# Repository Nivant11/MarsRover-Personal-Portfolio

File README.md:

# This is my personal portfolio of work that I have done on Cornell Mars Rover

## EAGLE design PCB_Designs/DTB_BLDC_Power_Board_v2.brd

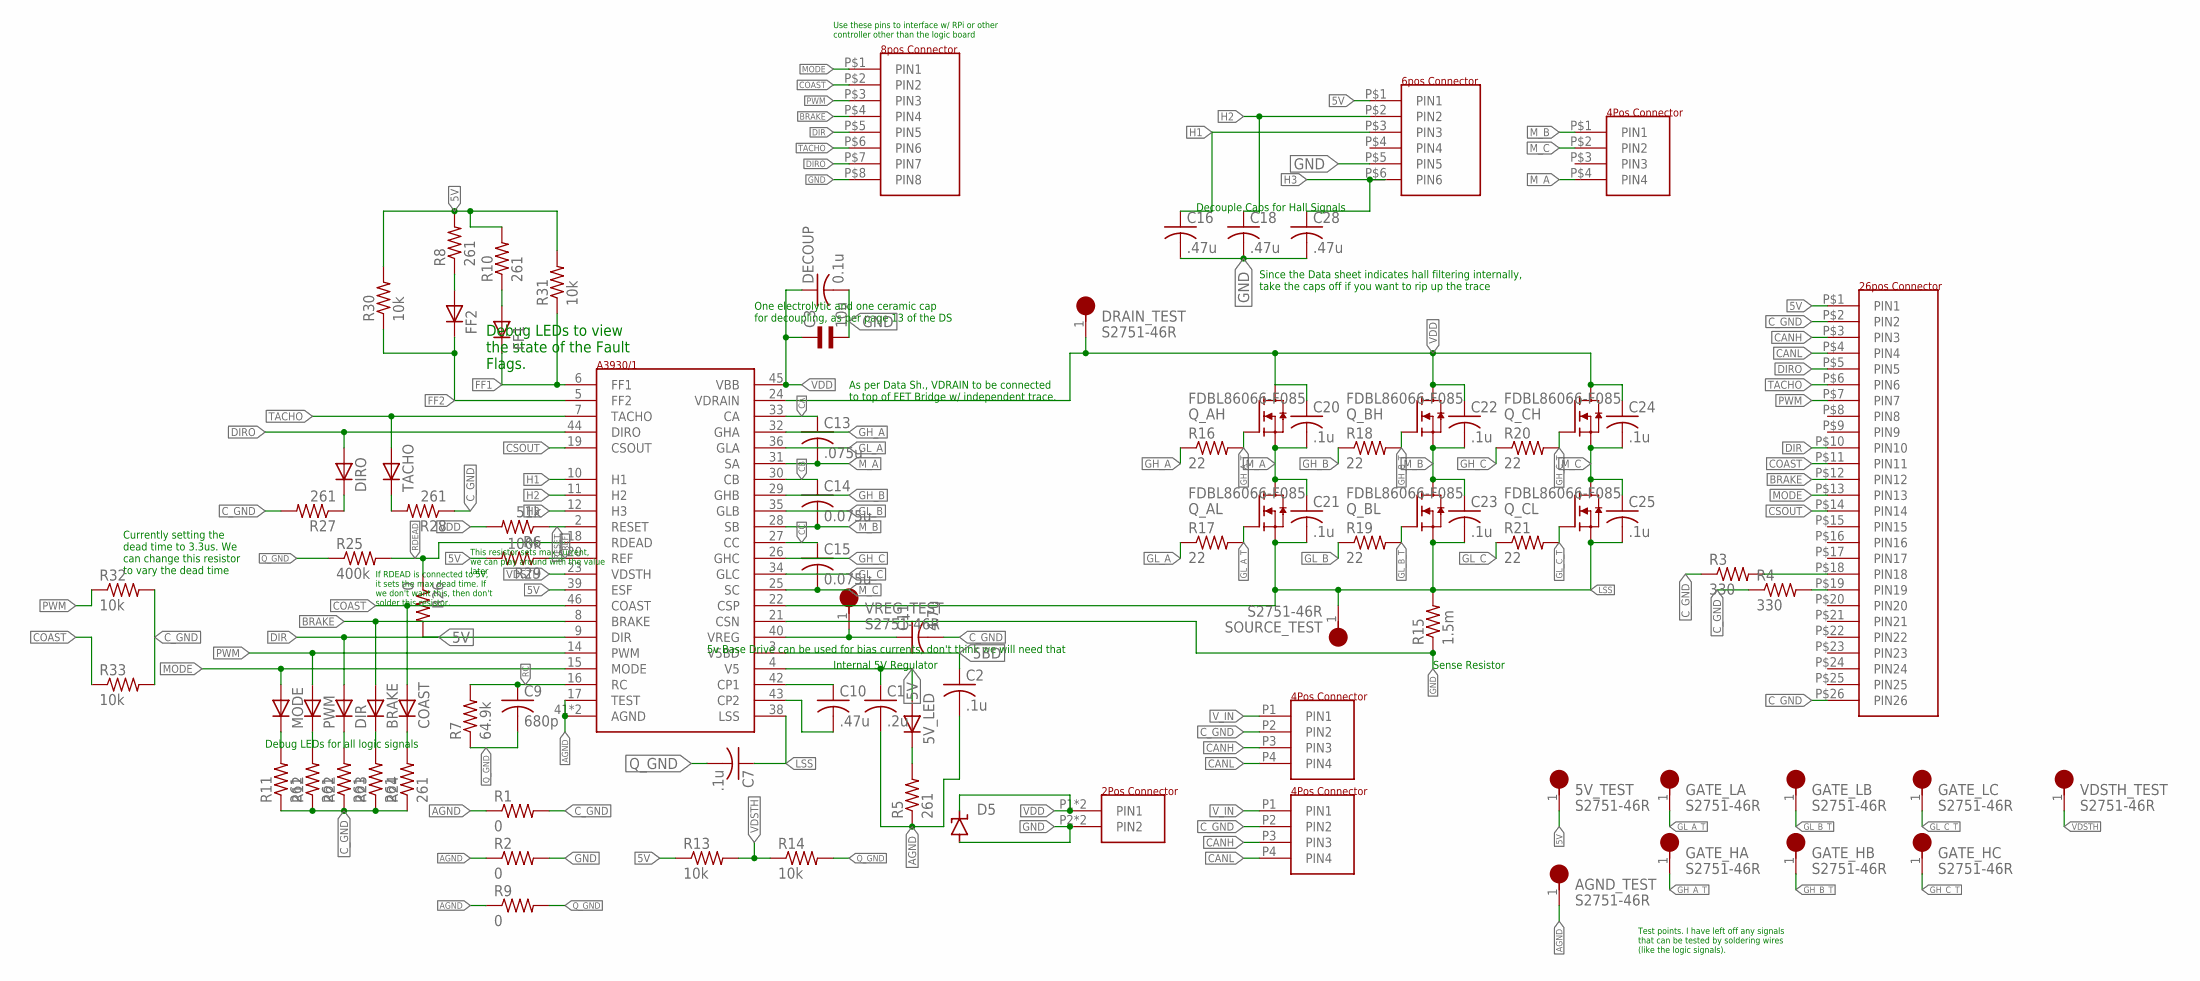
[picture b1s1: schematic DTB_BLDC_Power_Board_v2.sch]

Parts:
5V_LED: LED0603; DO0603
5V_TEST: S2751-46R; HARWIN_S2751-46R
AGND_TEST: S2751-46R; HARWIN_S2751-46R
BRAKE: LED0603; DO0603
C1: .2u; C1206K
C2, C20, C21, C22, C23, C24, C25: .1u; C1206K
C3: 10u; EU25-10
C7: .1u; C0603
C9: 680p; C0603K
C10: .47u; C1206K
C11: 4.7u; C1206K
C13: .075u; C1206K
C14, C15: 0.075u; C1206K
C16, C18, C28: .47u; C0603K
COAST: LED0603; DO0603
D5: SUPPRESSOR-SMBJ; SMBJ
DECOUP: 0.1u; C0603K
DIR: LED0603; DO0603
DIRO: LED0603; DO0603
DRAIN_TEST: S2751-46R; HARWIN_S2751-46R
FF1, FF2: LED0603; DO0603
GATE_HA: S2751-46R; HARWIN_S2751-46R
GATE_HB: S2751-46R; HARWIN_S2751-46R
GATE_HC: S2751-46R; HARWIN_S2751-46R
GATE_LA: S2751-46R; HARWIN_S2751-46R
GATE_LB: S2751-46R; HARWIN_S2751-46R
GATE_LC: S2751-46R; HARWIN_S2751-46R
J1: 26POS_CONNECTORN2526-6002-RB; N2526-6002-RB
J2: 4POS_MOLEX_MEGAFIT5.7; MOLEX_MEGAFIT5.7_1720650204
J3: 6POS_MOLEX_MINIFIT4.2; MOLEX_MINIFIT4.2_0460150606
J4, J5: 4POS_CONNECTORMOLEX_MICROFIT3.0_0430450412; MOLEX_MICROFIT3.0_0430450412
J6: 2POS_CONNECTORPOWERPOLE_45_1X2_VERT; POWERPOLE_45A_1X2_VERT
MODE: LED0603; DO0603
PWM: LED0603; DO0603
Q_AH: FDBL86066-F085; PG-HSOF-8-1
Q_AL: FDBL86066-F085; PG-HSOF-8-1
Q_BH: FDBL86066-F085; PG-HSOF-8-1
Q_BL: FDBL86066-F085; PG-HSOF-8-1
Q_CH: FDBL86066-F085; PG-HSOF-8-1
Q_CL: FDBL86066-F085; PG-HSOF-8-1
R1, R2, R9: 0; R1206
R3, R4: 330; R0603
R5, R8, R10, R11, R12, R22, R23, R24, R27, R28: 261; R0603
R6: 51k; R0603
R7: 64.9k; R0603
R13, R14, R30, R31, R32, R33: 10k; R0603
R15: 1.5m; R2512
R16, R17, R18, R19, R20, R21: 22; R1206
R25: 400k; R0603
R26: 0; R0603
R29: 100k; R0603
SOURCE_TEST: S2751-46R; HARWIN_S2751-46R
TACHO: LED0603; DO0603
U1: A3930/1; QFP50P900X900X160-49T500
U$13: 8POS_CONNECTOR8POS_HEADER_0.1"; 8POS_HEADER_.1"
VDSTH_TEST: S2751-46R; HARWIN_S2751-46R
VREG_TEST: S2751-46R; HARWIN_S2751-46R

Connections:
5BD: C2.1, U1.3 (V5BD)
5V: 5V_LED.1 (A), 5V_TEST.1, C1.1, J1.P$1 (PIN1), J3.P$1 (PIN1), R8.2, R10.2, R13.1, R26.2, R29.2, R30.2, R31.2, U1.4 (V5), U1.39 (ESF)
AGND: AGND_TEST.1, C1.2, C2.2, R1.1, R2.1, R5.1, R9.1, U1.17 (TEST), U1.41 (AGND), U1.49 (AGND)
BRAKE: BRAKE.1 (A), J1.P$12 (PIN12), U1.8 (BRAKE), U$13.P$4 (PIN4)
CA: C13.1, U1.33 (CA)
CANH: J1.P$3 (PIN3), J4.P3 (PIN3), J5.P3 (PIN3)
CANL: J1.P$4 (PIN4), J4.P4 (PIN4), J5.P4 (PIN4)
CB: C14.1, U1.30 (CB)
CC: C15.1, U1.27 (CC)
COAST: COAST.1 (A), J1.P$11 (PIN11), R33.1, U1.46 (COAST), U$13.P$2 (PIN2)
CSOUT: J1.P$14 (PIN14), U1.19 (CSOUT)
C_GND: C11.2, J1.P$2 (PIN2), J1.P$26 (PIN26), J4.P2 (PIN2), J5.P2 (PIN2), R1.2, R3.1, R4.1, R11.1, R12.1, R22.1, R23.1, R24.1, R27.2, R28.1, R32.2, R33.2
DIR: DIR.1 (A), J1.P$10 (PIN10), U1.9 (DIR), U$13.P$5 (PIN5)
DIRO: DIRO.1 (A), J1.P$5 (PIN5), U1.44 (DIRO), U$13.P$7 (PIN7)
FF1: FF1.2 (C), R31.1, U1.6 (FF1)
FF2: FF2.2 (C), R30.1, U1.5 (FF2)
GH_A: R16.1, U1.32 (GHA)
GH_A_T: GATE_HA.1, Q_AH.P$4 (G), R16.2
GH_B: R18.1, U1.29 (GHB)
GH_B_T: GATE_HB.1, Q_BH.P$4 (G), R18.2
GH_C: R20.1, U1.26 (GHC)
GH_C_T: GATE_HC.1, Q_CH.P$4 (G), R20.2
GL_A: R17.1, U1.36 (GLA)
GL_A_T: GATE_LA.1, Q_AL.P$4 (G), R17.2
GL_B: R19.1, U1.35 (GLB)
GL_B_T: GATE_LB.1, Q_BL.P$4 (G), R19.2
GL_C: R21.1, U1.34 (GLC)
GL_C_T: GATE_LC.1, Q_CL.P$4 (G), R21.2
GND: C3.2, C16.2, C18.2, C28.2, D5.A, DECOUP.2, J3.P$5 (PIN5), J6.P2 (PIN2), J6.P2B (PIN2), R2.2, R15.1, U1.21 (CSN), U$13.P$8 (PIN8)
H1: C16.1, J3.P$3 (PIN3), U1.10 (H1)
H2: C18.1, J3.P$2 (PIN2), U1.11 (H2)
H3: C28.1, J3.P$6 (PIN6), U1.12 (H3)
LSS: C7.1, C21.2, C23.2, C25.2, Q_AL.P$5 (S), Q_AL.P$6 (S), Q_AL.P$7 (S), Q_AL.P$8 (S), Q_AL.P$9 (S), Q_AL.P$10 (S), Q_AL.P$11 (S), Q_AL.P$12 (S), Q_BL.P$5 (S), Q_BL.P$6 (S), Q_BL.P$7 (S), Q_BL.P$8 (S), Q_BL.P$9 (S), Q_BL.P$10 (S), Q_BL.P$11 (S), Q_BL.P$12 (S), Q_CL.P$5 (S), Q_CL.P$6 (S), Q_CL.P$7 (S), Q_CL.P$8 (S), Q_CL.P$9 (S), Q_CL.P$10 (S), Q_CL.P$11 (S), Q_CL.P$12 (S), R15.2, SOURCE_TEST.1, U1.22 (CSP), U1.38 (LSS)
MODE: J1.P$13 (PIN13), MODE.1 (A), U1.15 (MODE), U$13.P$1 (PIN1)
M_A: C13.2, C20.2, C21.1, J2.P$4 (PIN4), Q_AH.P$5 (S), Q_AH.P$6 (S), Q_AH.P$7 (S), Q_AH.P$8 (S), Q_AH.P$9 (S), Q_AH.P$10 (S), Q_AH.P$11 (S), Q_AH.P$12 (S), Q_AL.P$1 (D), Q_AL.P$2 (D), Q_AL.P$3 (D), U1.31 (SA)
M_B: C14.2, C22.2, C23.1, J2.P$1 (PIN1), Q_BH.P$5 (S), Q_BH.P$6 (S), Q_BH.P$7 (S), Q_BH.P$8 (S), Q_BH.P$9 (S), Q_BH.P$10 (S), Q_BH.P$11 (S), Q_BH.P$12 (S), Q_BL.P$1 (D), Q_BL.P$2 (D), Q_BL.P$3 (D), U1.28 (SB)
M_C: C15.2, C24.2, C25.1, J2.P$2 (PIN2), Q_CH.P$5 (S), Q_CH.P$6 (S), Q_CH.P$7 (S), Q_CH.P$8 (S), Q_CH.P$9 (S), Q_CH.P$10 (S), Q_CH.P$11 (S), Q_CH.P$12 (S), Q_CL.P$1 (D), Q_CL.P$2 (D), Q_CL.P$3 (D), U1.25 (SC)
unnamed: J1.P$18 (PIN18), R3.2
unnamed: J1.P$19 (PIN19), R4.2
unnamed: C10.1, U1.42 (CP1)
unnamed: C10.2, U1.43 (CP2)
unnamed: FF1.1 (A), R10.1
unnamed: 5V_LED.2 (C), R5.2
unnamed: FF2.1 (A), R8.1
unnamed: DIRO.2 (C), R27.1
unnamed: R28.2, TACHO.2 (C)
unnamed: MODE.2 (C), R11.2
unnamed: PWM.2 (C), R12.2
unnamed: DIR.2 (C), R22.2
unnamed: BRAKE.2 (C), R23.2
unnamed: COAST.2 (C), R24.2
PWM: J1.P$7 (PIN7), PWM.1 (A), R32.1, U1.14 (PWM), U$13.P$3 (PIN3)
Q_GND: C7.2, C9.2, R7.1, R9.2, R14.2, R25.1
RC: C9.1, R7.2, U1.16 (RC)
RDEAD: R25.2, R26.1, U1.18 (RDEAD)
REF: R29.1, U1.20 (REF)
RESET: R6.1, U1.2 (RESET)
TACHO: J1.P$6 (PIN6), TACHO.1 (A), U1.7 (TACHO), U$13.P$6 (PIN6)
VDD: C3.1, C20.1, C22.1, C24.1, D5.C, DECOUP.1, DRAIN_TEST.1, J6.P1 (PIN1), J6.P1B (PIN1), Q_AH.P$1 (D), Q_AH.P$2 (D), Q_AH.P$3 (D), Q_BH.P$1 (D), Q_BH.P$2 (D), Q_BH.P$3 (D), Q_CH.P$1 (D), Q_CH.P$2 (D), Q_CH.P$3 (D), R6.2, U1.24 (VDRAIN), U1.45 (VBB)
VDSTH: R13.2, R14.1, U1.23 (VDSTH), VDSTH_TEST.1
VREG: C11.1, U1.40 (VREG), VREG_TEST.1
V_IN: J4.P1 (PIN1), J5.P1 (PIN1)

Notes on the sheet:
Internal 5V Regulator
5v Base Drive can be used for bias currents, don't think we will need that
Decouple Caps for Hall Signals
Since the Data sheet indicates hall filtering internally, take the caps off if you want to rip up the trace
If RDEAD is connected to 5V, it sets the max dead time. If we don't want this, then don't solder this resistor.
Currently setting the dead time to 3.3us. We can change this resistor to vary the dead time
As per Data Sh., VDRAIN to be connected to top of FET Bridge w/ independent trace.
Debug LEDs to view the state of the Fault Flags.
One electrolytic and one ceramic cap for decoupling, as per page 13 of the DS
Debug LEDs for all logic signals
Sense Resistor
This resistor sets max current, we can play around with the value later
Test points. I have left off any signals that can be tested by soldering wires (like the logic signals).
Use these pins to interface w/ RPi or other controller other than the logic board

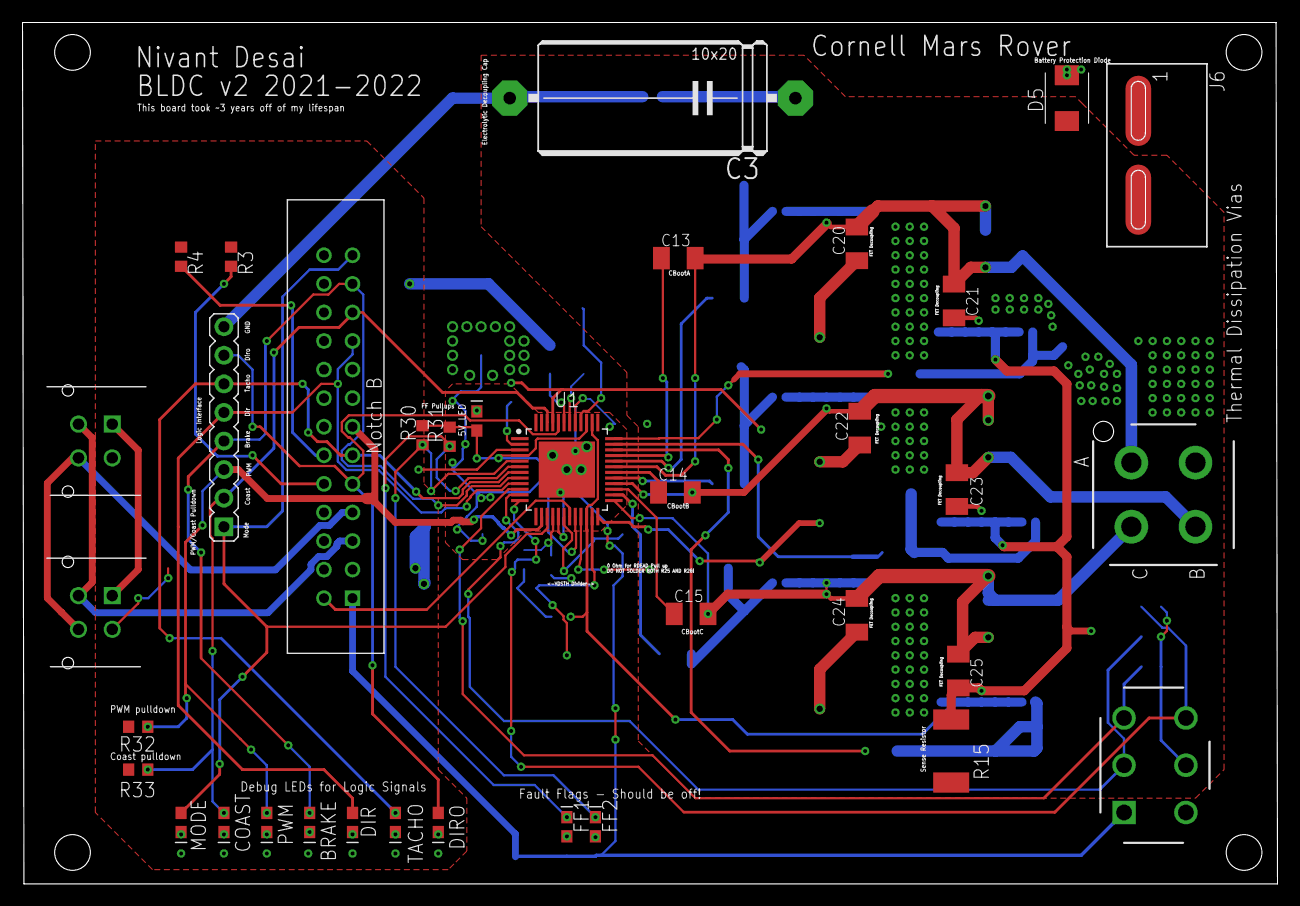
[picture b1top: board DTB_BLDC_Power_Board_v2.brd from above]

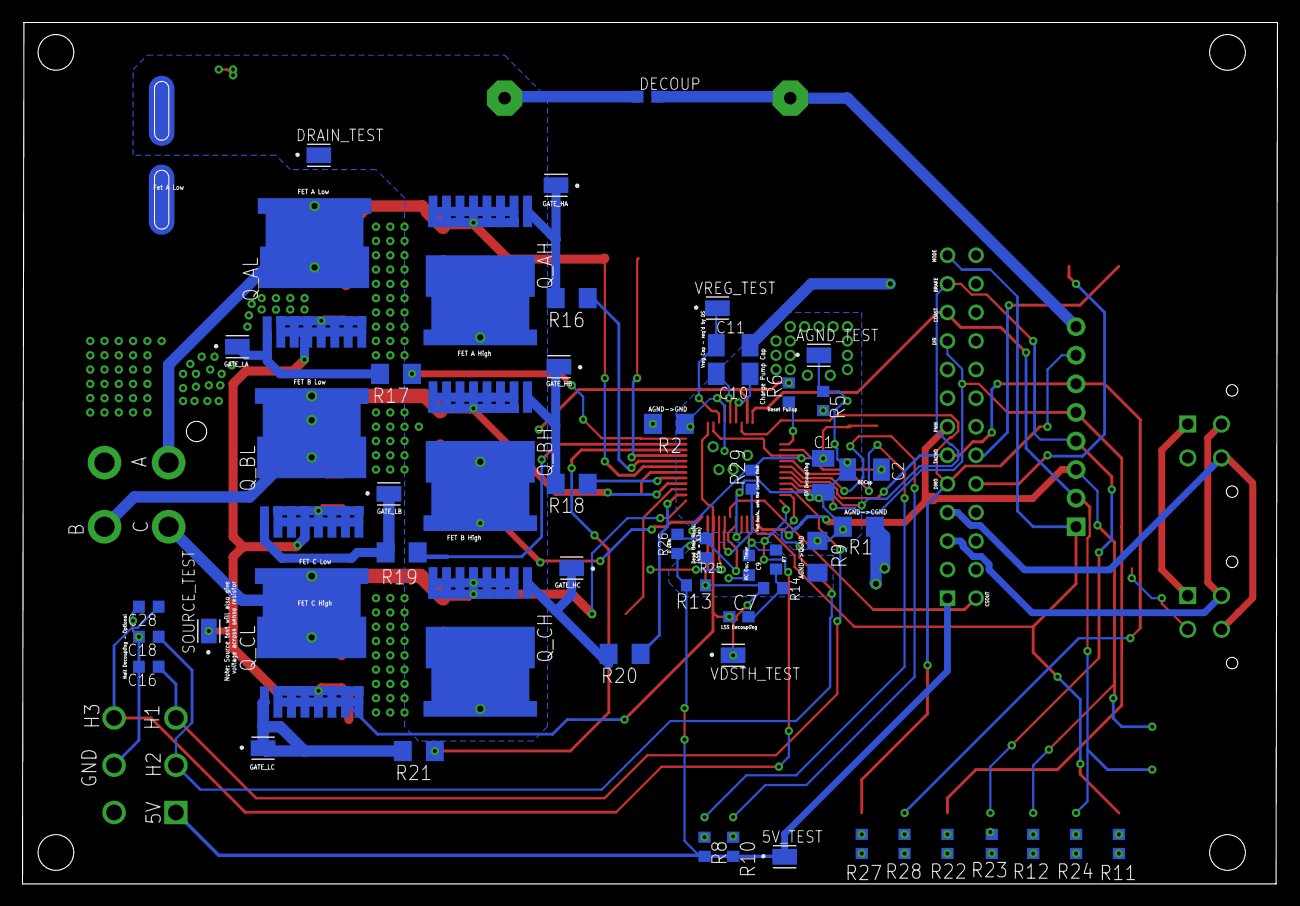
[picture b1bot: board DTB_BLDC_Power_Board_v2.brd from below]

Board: 2 copper layers, 111.6 x 76.6 mm, 90 parts (54 on the bottom side), 62 nets.

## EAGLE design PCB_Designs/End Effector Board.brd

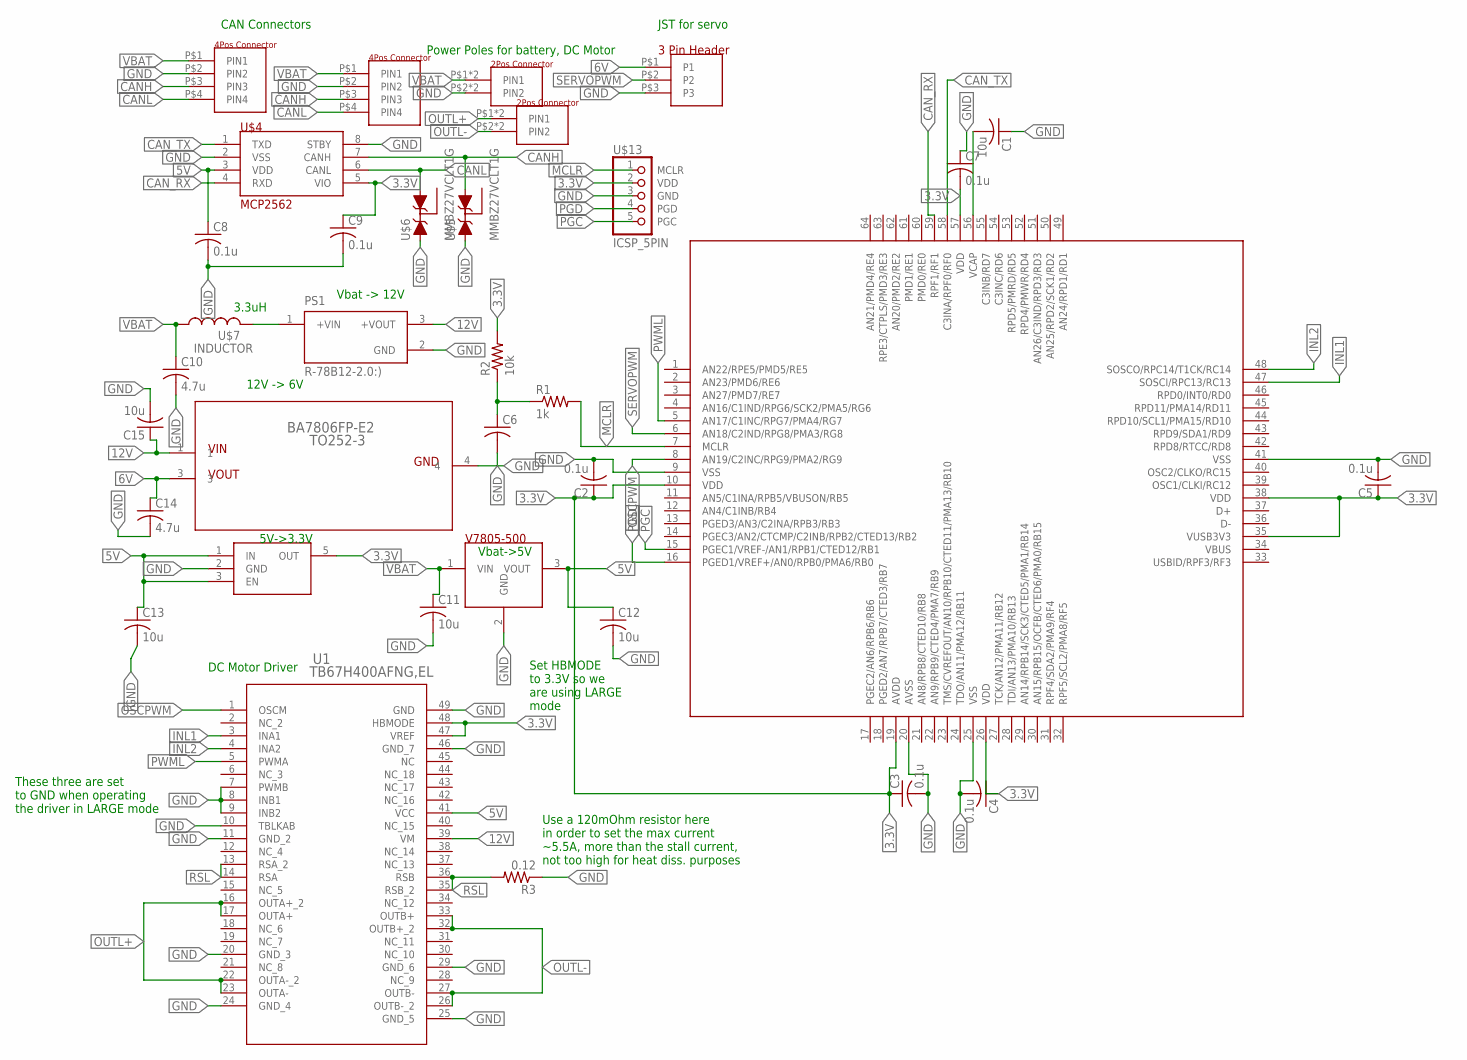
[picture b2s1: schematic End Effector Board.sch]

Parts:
BA7806FP-E2: TO252-3
C1, C11, C12, C13, C15: 10u; C0603
C2, C3, C4, C5, C7, C8, C9: 0.1u; C0603
C6: C-USC0603; C0603
C10, C14: 4.7u; C0603
PS1: R-78B12-2.0:); CONV_R-78B12-2.0
R1: 1k; R0603
R2: 10k; R0603
R3: 0.12; R0603
U1: TB67H400AFNG,EL; HTSSOP48-P-300-0P50_TOS
U$1, U$2: 4POS_2ROW_CONNECTOR; 4POS_2ROW_HEADER_.1"
U$3: PIC32MX530F128HOLD; TQFP64-10X10X1MM
U$4: MCP2562; SOIC8
U$5, U$6: MMBZ27VCLT1G; SOT23
U$7: INDUCTOR; 0603
U$8: TLV70233DBVR; SOT-23-5
U$9: V7805-500; SIP3
U$10, U$11: 2POS_CONNECTOR,1X2_45A_POWERPOLE; POWERPOLE_45A_1X2
U$12: 3POS_CONNECTORJST-ZH; 3POS_ZH_SIDE
U$13: ICSP_5PIN; ICSP_5

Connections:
3.3V: C2.1, C3.1, C4.1, C5.1, C7.2, C9.1, R2.2, U1.47 (VREF), U1.48 (HBMODE), U$3.10 (VDD), U$3.19 (AVDD), U$3.26 (VDD), U$3.35 (VUSB3V3), U$3.38 (VDD), U$3.57 (VDD), U$4.5 (VIO), U$8.5 (OUT), U$13.2 (VDD)
5V: C8.1, C12.1, C13.1, U1.41 (VCC), U$4.3 (VDD), U$8.1 (IN), U$8.3 (EN), U$9.3 (VOUT)
6V: BA7806FP-E2.3, C14.1, U$12.P$1 (P1)
12V: BA7806FP-E2.1, C15.1, PS1.3 (+VOUT), U1.39 (VM)
CANH: U$1.P$3 (PIN3), U$2.P$3 (PIN3), U$4.7 (CANH), U$5.2 (A2)
CANL: U$1.P$4 (PIN4), U$2.P$4 (PIN4), U$4.6 (CANL), U$6.2 (A2)
CAN_RX: U$3.59 (RPF1/RF1), U$4.4 (RXD)
CAN_TX: U$3.58 (C3INA/RPF0/RF0), U$4.1 (TXD)
GND: BA7806FP-E2.4, C1.1, C2.2, C3.2, C4.2, C5.2, C6.2, C7.1, C8.2, C9.2, C10.2, C11.2, C12.2, C13.2, C14.2, C15.2, PS1.2 (GND), R3.1, U1.7 (PWMB), U1.8 (INB1), U1.9 (INB2), U1.10 (TBLKAB), U1.11 (GND_2), U1.20 (GND_3), U1.24 (GND_4), U1.25 (GND_5), U1.29 (GND_6), U1.46 (GND_7), U1.49 (GND), U$1.P$2 (PIN2), U$2.P$2 (PIN2), U$3.9 (VSS), U$3.20 (AVSS), U$3.25 (VSS), U$3.41 (VSS), U$4.2 (VSS), U$4.8 (STBY), U$5.1 (A1), U$6.1 (A1), U$8.2 (GND), U$9.2 (GND), U$10.P$2 (PIN2), U$10.P$6 (PIN2), U$12.P$3 (P3), U$13.3 (GND)
INL1: U1.3 (INA1), U$3.47 (SOSCI/RPC13/RC13)
INL2: U1.4 (INA2), U$3.48 (SOSCO/RPC14/T1CK/RC14)
MCLR: R1.2, U$3.7 (MCLR), U$13.1 (MCLR)
unnamed: C1.2, U$3.56 (VCAP)
unnamed: PS1.1 (+VIN), U$7.2
unnamed: C6.1, R1.1, R2.1
OSCPWM: U1.1 (OSCM), U$3.8 (AN19/C2INC/RPG9/PMA2/RG9)
OUTL+: U1.16 (OUTA+_2), U1.17 (OUTA+), U1.22 (OUTA-_2), U1.23 (OUTA-), U$11.P$1 (PIN1), U$11.P$5 (PIN1)
OUTL-: U1.26 (OUTB-_2), U1.27 (OUTB-), U1.32 (OUTB+_2), U1.33 (OUTB+), U$11.P$2 (PIN2), U$11.P$6 (PIN2)
PGC: U$3.15 (PGEC1/VREF-/AN1/RPB1/CTED12/RB1), U$13.5 (PGC)
PGD: U$3.16 (PGED1/VREF+/AN0/RPB0/PMA6/RB0), U$13.4 (PGD)
PWML: U1.5 (PWMA), U$3.5 (AN17/C1INC/RPG7/PMA4/RG7)
RSL: R3.2, U1.13 (RSA_2), U1.14 (RSA), U1.35 (RSB_2), U1.36 (RSB)
SERVOPWM: U$3.6 (AN18/C2IND/RPG8/PMA3/RG8), U$12.P$2 (P2)
VBAT: C10.1, C11.1, U$1.P$1 (PIN1), U$2.P$1 (PIN1), U$7.1, U$9.1 (VIN), U$10.P$1 (PIN1), U$10.P$5 (PIN1)

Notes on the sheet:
DC Motor Driver
Vbat -> 12V
12V -> 6V
Vbat->5V
5V->3.3V
CAN Connectors
Power Poles for battery, DC Motor
JST for servo
Use a 120mOhm resistor here in order to set the max current ~5.5A, more than the stall current, not too high for heat diss. purposes
Set HBMODE to 3.3V so we are using LARGE mode
These three are set to GND when operating the driver in LARGE mode
3.3uH

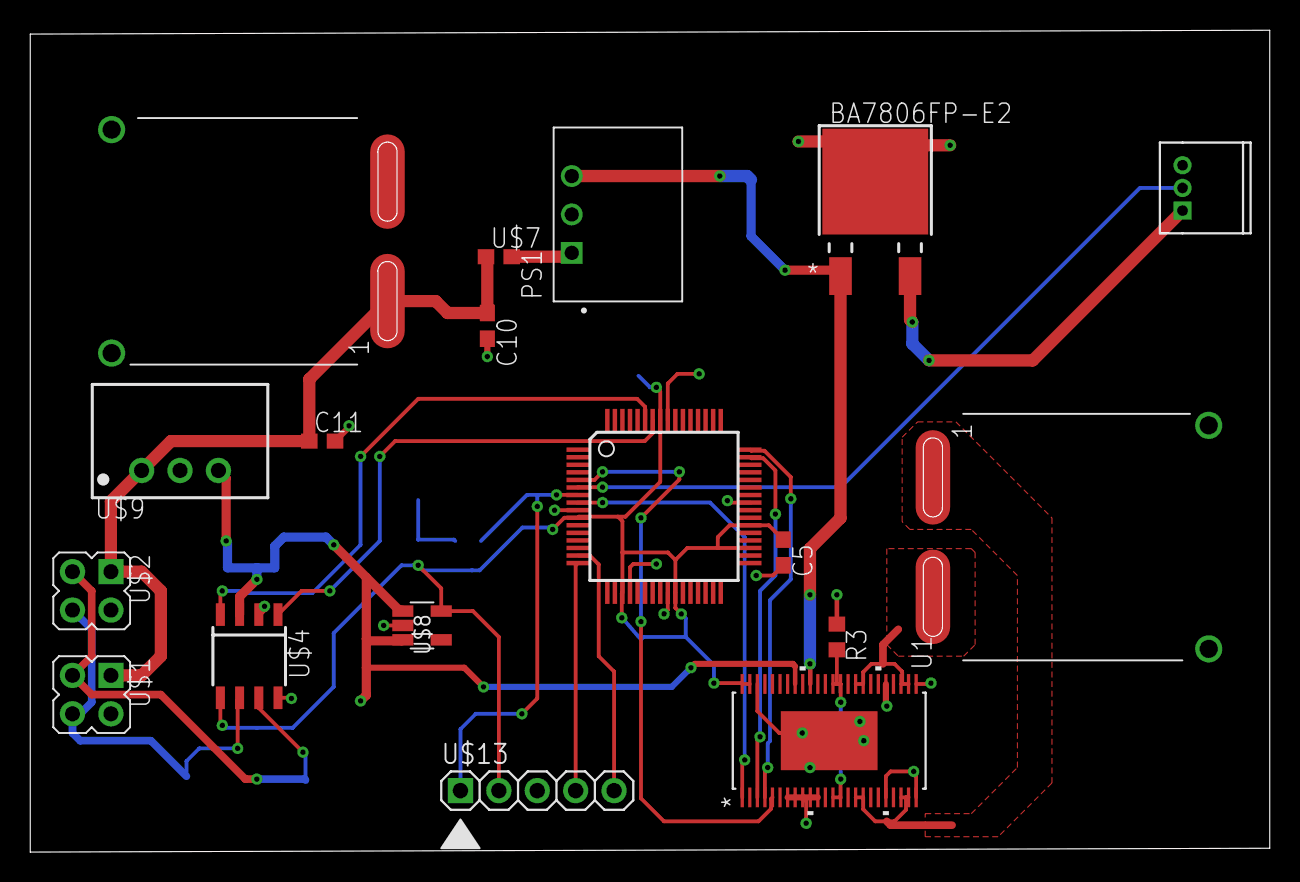
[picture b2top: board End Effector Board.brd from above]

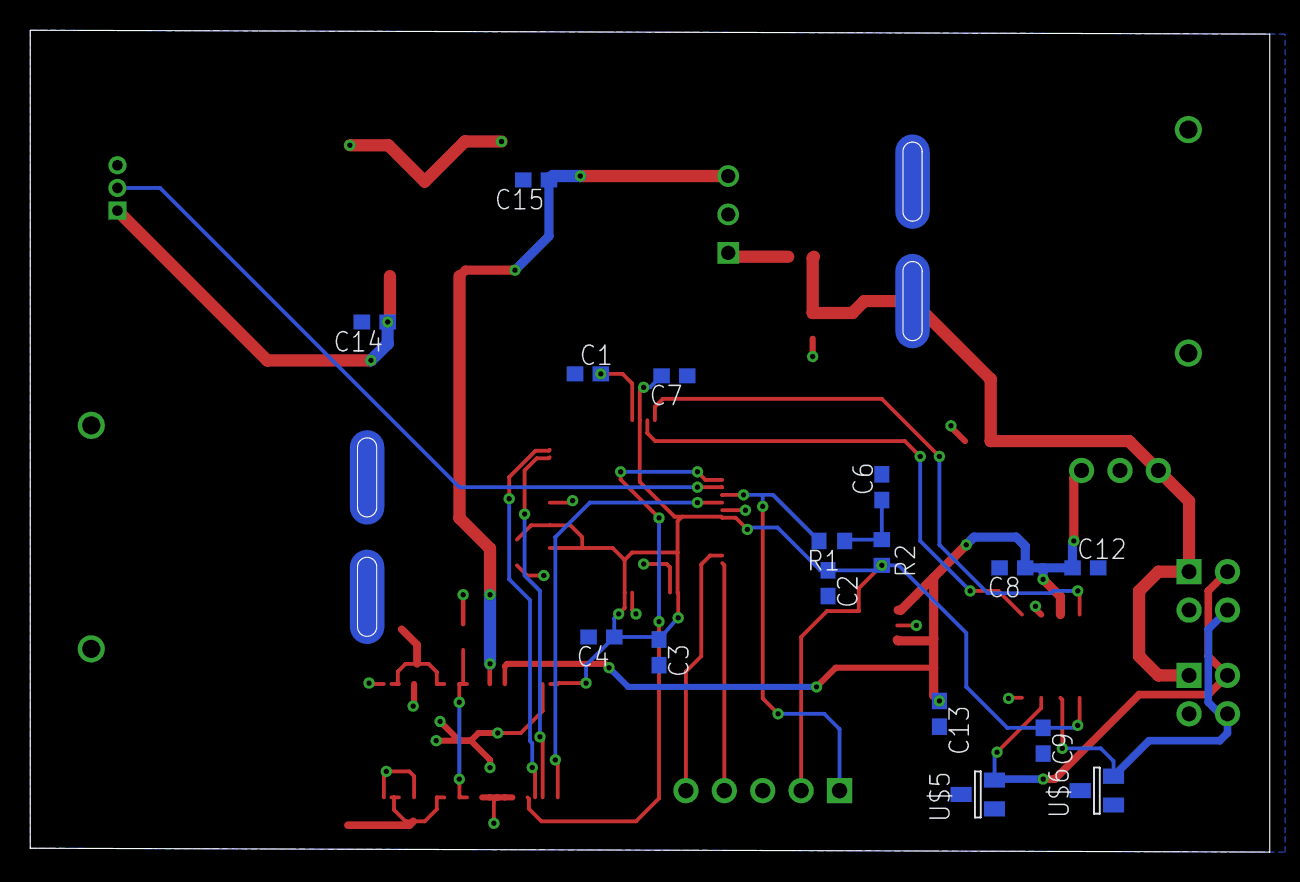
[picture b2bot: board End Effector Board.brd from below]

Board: 2 copper layers, 82.0 x 54.3 mm, 34 parts (16 on the bottom side), 24 nets.

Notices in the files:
parts and their libraries:
COPYRIGHT: Copyright (C) 2021 Ultra Librarian. All rights reserved.
